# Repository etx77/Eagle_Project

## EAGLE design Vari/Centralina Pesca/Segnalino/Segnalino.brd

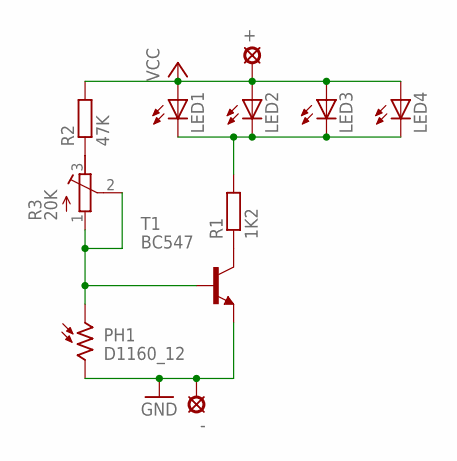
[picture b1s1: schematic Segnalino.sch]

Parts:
+: LSP10
-: LSP10
LED1, LED2, LED3, LED4: LED10MM
PH1: D1160_12; D11XX
R1: 1K2; 0204V
R2: 47K; 0204V
R3: 20K; RTRIM3339P
T1: BC547; TO92

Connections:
GND: -.MP, PH1.2, T1.1 (E)
unnamed: R1.1, T1.3 (C)
unnamed: R2.1, R3.3 (E)
unnamed: PH1.1, R3.1 (A), R3.2 (S), T1.2 (B)
unnamed: LED1.K (C), LED2.K (C), LED3.K (C), LED4.K (C), R1.2
VCC: +.MP, LED1.A, LED2.A, LED3.A, LED4.A, R2.2

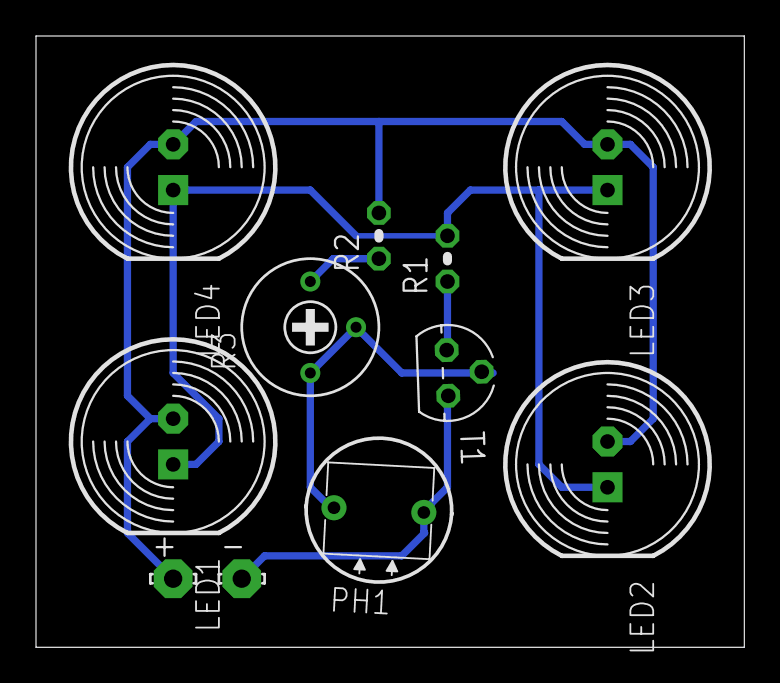
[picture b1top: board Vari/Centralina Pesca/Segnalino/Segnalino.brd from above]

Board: 2 copper layers, 39.4 x 34.0 mm, 11 parts (0 on the bottom side), 6 nets.

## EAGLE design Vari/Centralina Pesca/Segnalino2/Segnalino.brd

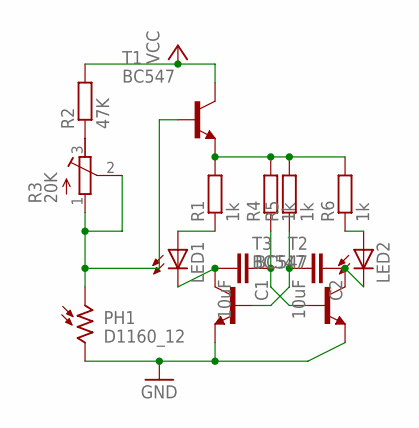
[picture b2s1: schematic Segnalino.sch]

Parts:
C1, C2: 10uF; C025-024X044
LED1, LED2: LED3MM
PH1: D1160_12; D11XX
R1, R4, R5, R6: 1k; 0204V
R2: 47K; 0204V
R3: 20K; RTRIM3339P
T1, T2, T3: BC547; TO92

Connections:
GND: PH1.2, T2.1 (E), T3.1 (E)
unnamed: C1.2, LED1.K (C), T2.3 (C)
unnamed: R2.1, R3.3 (E)
unnamed: C1.1, R4.1, T3.2 (B)
unnamed: PH1.1, R3.1 (A), R3.2 (S), T1.2 (B)
unnamed: R1.2, R4.2, R5.2, R6.2, T1.1 (E)
unnamed: C2.2, R5.1, T2.2 (B)
unnamed: LED1.A, R1.1
unnamed: LED2.A, R6.1
unnamed: C2.1, LED2.K (C), T3.3 (C)
VCC: R2.2, T1.3 (C)

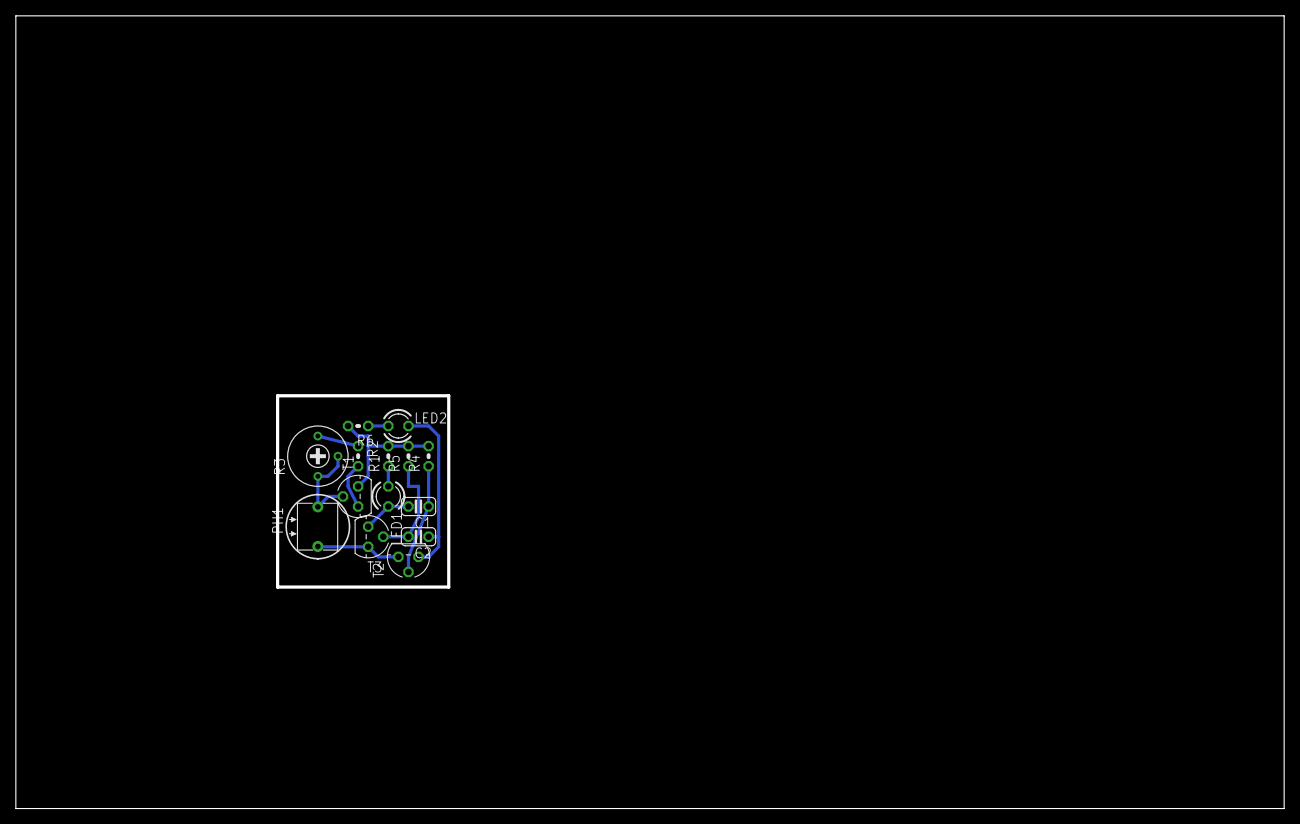
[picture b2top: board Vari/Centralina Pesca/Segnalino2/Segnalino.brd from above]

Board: 2 copper layers, 160.0 x 100.0 mm, 14 parts (0 on the bottom side), 11 nets.

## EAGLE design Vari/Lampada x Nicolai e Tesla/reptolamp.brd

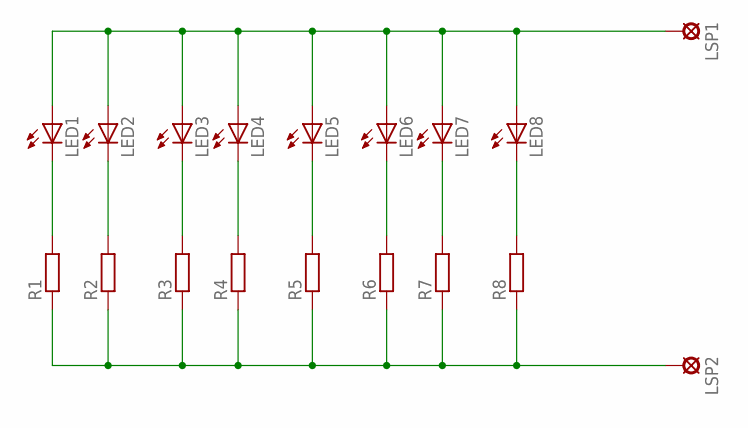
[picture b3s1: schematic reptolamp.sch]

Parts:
LED1, LED2, LED3, LED4, LED5, LED6, LED7, LED8: LED5MM
LSP1, LSP2: LSP10
R1, R2, R3, R4, R5, R6, R7, R8: R-EU_0207/10; 0207/10

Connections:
unnamed: LSP2.MP, R1.1, R2.1, R3.1, R4.1, R5.1, R6.1, R7.1, R8.1
unnamed: LED1.K (C), R1.2
unnamed: LED2.K (C), R2.2
unnamed: LED3.K (C), R3.2
unnamed: LED4.K (C), R4.2
unnamed: LED5.K (C), R5.2
unnamed: LED6.K (C), R6.2
unnamed: LED7.K (C), R7.2
unnamed: LED8.K (C), R8.2
unnamed: LED1.A, LED2.A, LED3.A, LED4.A, LED5.A, LED6.A, LED7.A, LED8.A, LSP1.MP

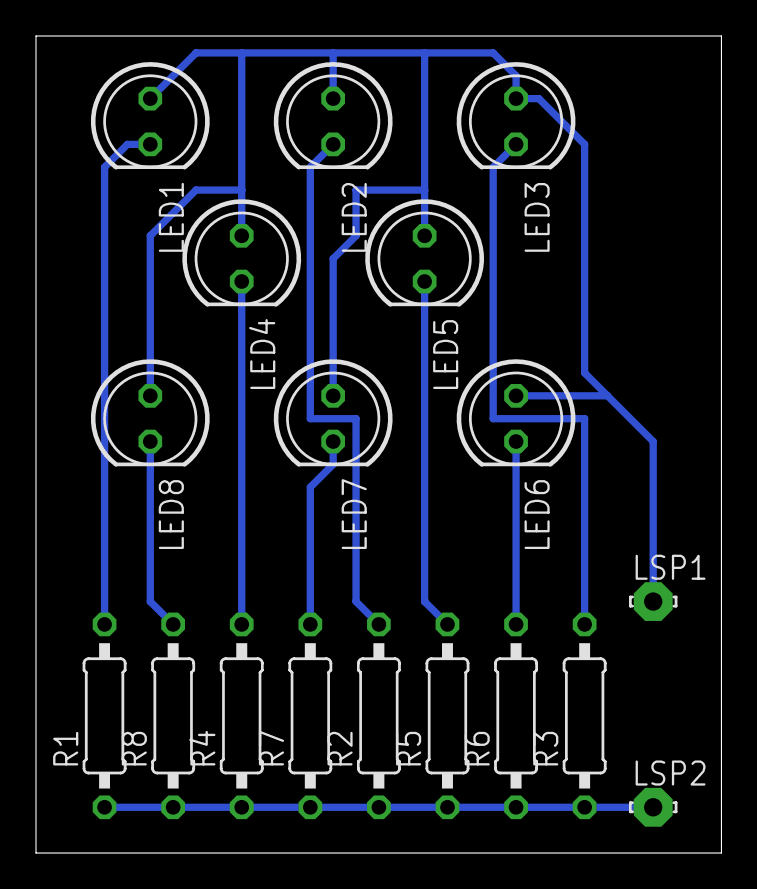
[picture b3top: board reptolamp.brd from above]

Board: 2 copper layers, 38.1 x 45.4 mm, 18 parts (0 on the bottom side), 10 nets.
